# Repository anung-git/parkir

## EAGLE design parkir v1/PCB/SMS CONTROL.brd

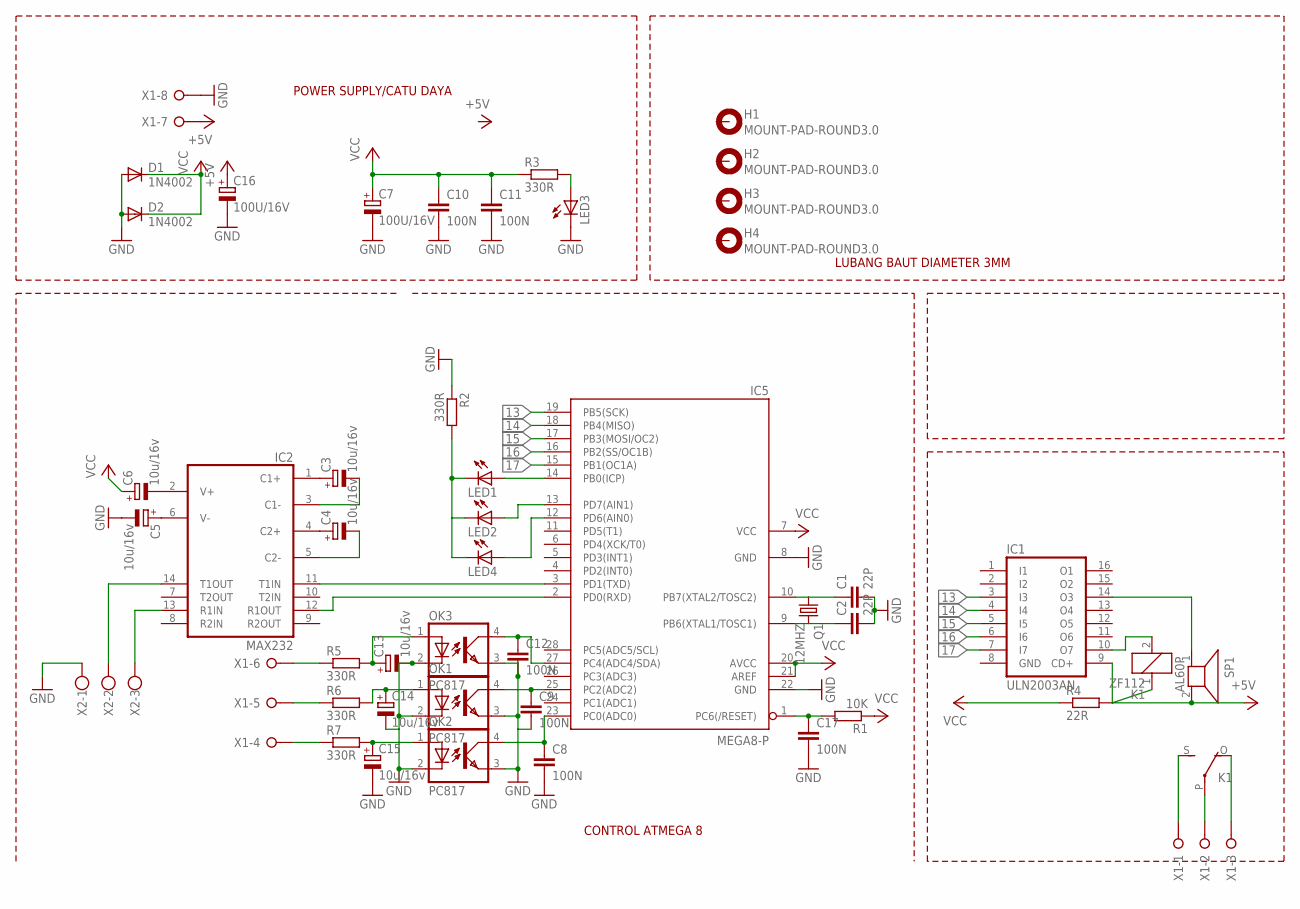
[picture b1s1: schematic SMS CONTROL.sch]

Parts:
C1, C2: 22P; C025-025X050
C3, C4, C5, C6, C13, C14, C15: 10u/16v; E2,5-6
C7, C16: 100U/16V; E2,5-6
C8, C9, C11, C12, C17: 100N; C025-025X050
C10: 100N; C075-032X103
D1, D2: 1N4002; DO35-10
H1, H2, H3, H4: MOUNT-PAD-ROUND3.0; 3,0-PAD
IC1: ULN2003AN; DIL16
IC2: MAX232; DIL16
IC5: MEGA8-P; DIL28-3
K1: ZF112
LED1, LED2, LED3, LED4: LED5MM
OK1, OK2, OK3: PC817; DIL04
Q1: 12MHZ; HC49U-V
R1: 10K; 0207/10
R2, R3, R5, R6, R7: 330R; 0207/10
R4: 22R; 0207/10
SP1: AL60P
X1: W237-08P; W237-8P
X2: W237-103

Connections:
13: IC1.3 (I3), IC5.19 (PB5(SCK))
14: IC1.4 (I4), IC5.18 (PB4(MISO))
15: IC1.5 (I5), IC5.17 (PB3(MOSI/OC2))
16: IC1.6 (I6), IC5.16 (PB2(SS/OC1B))
17: IC1.7 (I7), IC5.15 (PB1(OC1A))
+5V: C16.+, IC1.9 (CD+), K1.1, R4.2, SP1.2, X1.7
GND: C1.2, C2.2, C5.-, C7.-, C8.2, C9.2, C10.2, C11.2, C12.2, C13.-, C14.-, C15.-, C16.-, C17.2, D1.A, D2.A, IC1.8 (GND), IC2.15 (GND), IC5.8 (GND), IC5.22 (GND), LED3.K (C), OK1.2 (C), OK1.3 (EMIT), OK2.2 (C), OK2.3 (EMIT), OK3.2 (C), OK3.3 (EMIT), R2.1, X1.8, X2.1
unnamed: C17.1, IC5.1 (PC6(/RESET)), R1.2
unnamed: C13.+, OK3.1 (A), R5.2
unnamed: C14.+, OK1.1 (A), R6.2
unnamed: C9.1, IC5.25 (PC2(ADC2)), OK1.4 (COL)
unnamed: C12.1, IC5.27 (PC4(ADC4/SDA)), OK3.4 (COL)
unnamed: C15.+, OK2.1 (A), R7.2
unnamed: R5.1, X1.6
unnamed: IC5.14 (PB0(ICP)), LED1.A
unnamed: IC2.12 (R1OUT), IC5.2 (PD0(RXD))
unnamed: IC2.11 (T1IN), IC5.3 (PD1(TXD))
unnamed: C2.1, IC5.9 (PB6(XTAL1/TOSC1)), Q1.2
unnamed: C1.1, IC5.10 (PB7(XTAL2/TOSC2)), Q1.1
unnamed: LED3.A, R3.2
unnamed: R6.1, X1.5
unnamed: C3.+, IC2.1 (C1+)
unnamed: C3.-, IC2.3 (C1-)
unnamed: C8.1, IC5.23 (PC0(ADC0)), OK2.4 (COL)
unnamed: IC5.13 (PD7(AIN1)), LED2.A
unnamed: LED1.K (C), LED2.K (C), LED4.K (C), R2.2
unnamed: R7.1, X1.4
unnamed: C4.+, IC2.4 (C2+)
unnamed: C4.-, IC2.5 (C2-)
unnamed: C5.+, IC2.6 (V-)
unnamed: C6.-, IC2.2 (V+)
unnamed: IC2.13 (R1IN), X2.3
unnamed: IC2.14 (T1OUT), X2.2
unnamed: IC5.12 (PD6(AIN0)), LED4.A
unnamed: K1.S, X1.1
unnamed: K1.P, X1.2
unnamed: K1.O, X1.3
unnamed: IC1.10 (O7), K1.2
unnamed: IC1.14 (O3), SP1.1
VCC: C6.+, C7.+, C10.1, C11.1, D1.C, D2.C, IC2.16 (VCC), IC5.7 (VCC), IC5.20 (AVCC), IC5.21 (AREF), R1.1, R3.1, R4.1

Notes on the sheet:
POWER SUPPLY/CATU DAYA
CONTROL ATMEGA 8
LUBANG BAUT DIAMETER 3MM

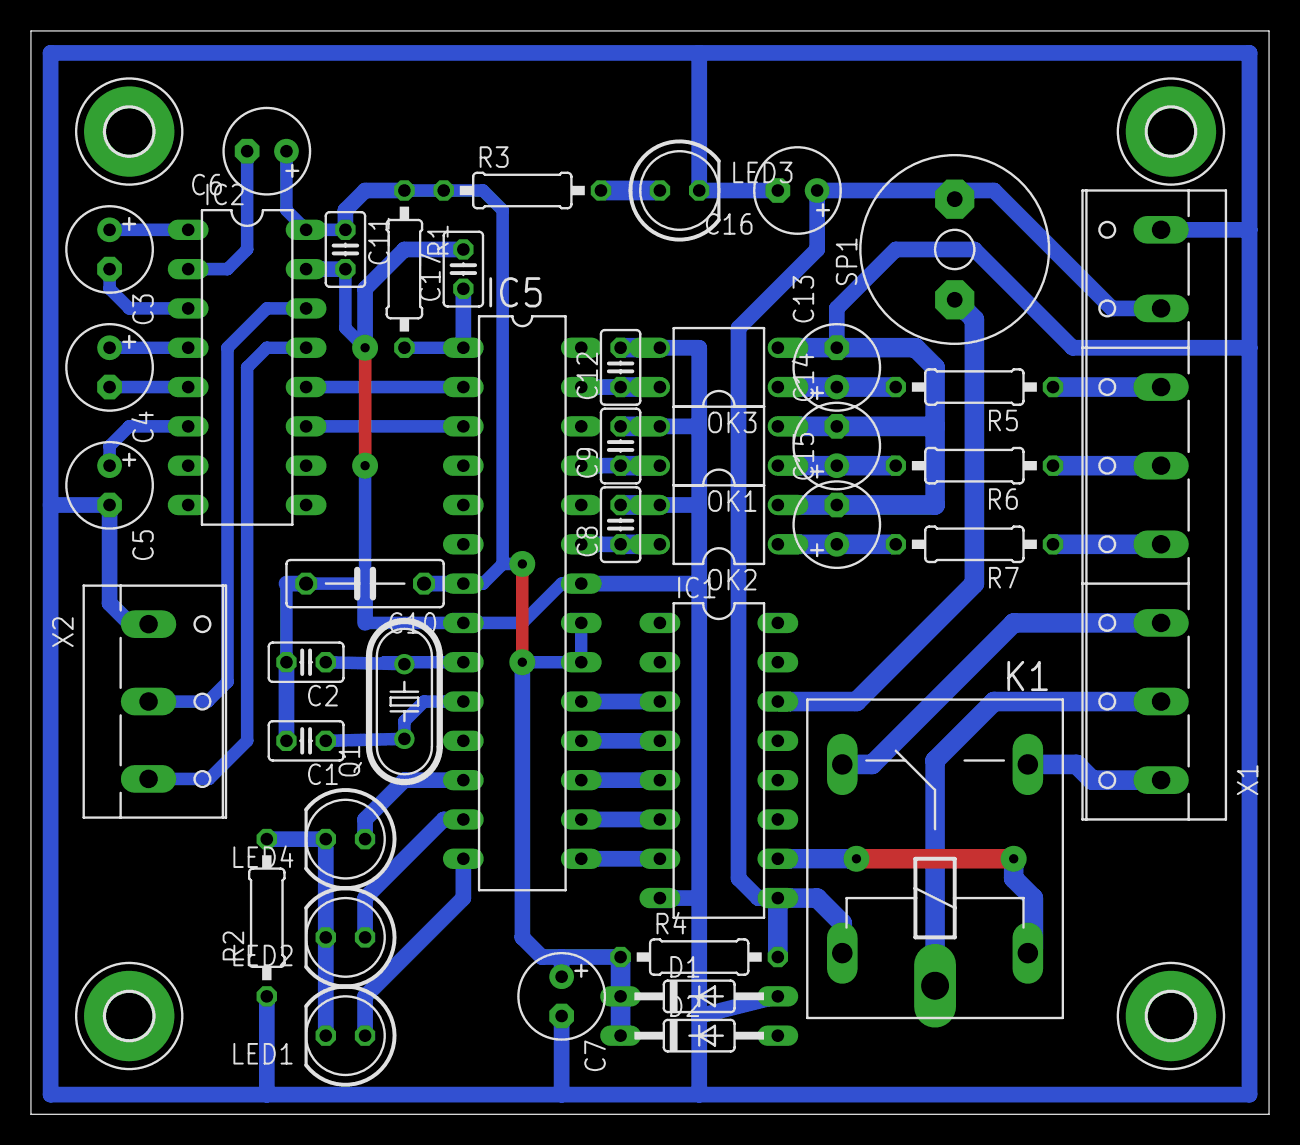
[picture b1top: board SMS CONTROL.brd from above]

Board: 2 copper layers, 80.0 x 70.0 mm, 45 parts (0 on the bottom side), 40 nets.

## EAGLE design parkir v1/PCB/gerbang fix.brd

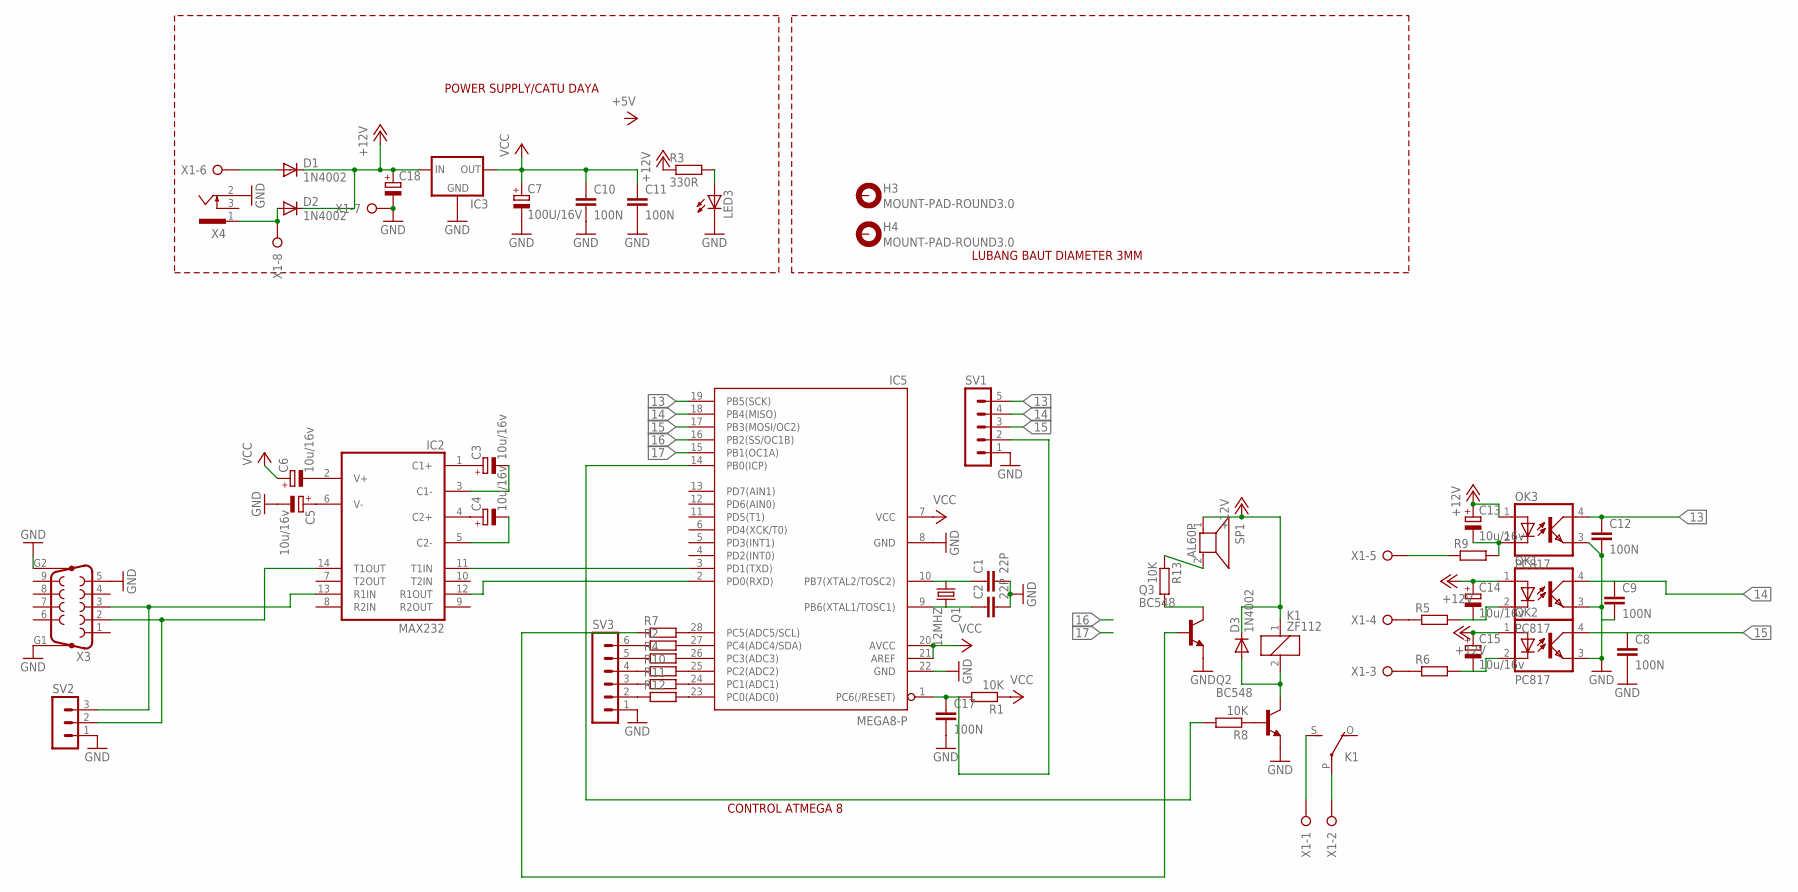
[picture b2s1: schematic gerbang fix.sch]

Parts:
C1, C2: 22P; C025-025X050
C3, C4, C5, C6, C13, C14, C15: 10u/16v; E2,5-6
C7: 100U/16V; E2,5-6
C8, C9, C10, C11, C12, C17: 100N; C025-025X050
C18: CPOL-EUE5-8.5; E5-8,5
D1, D2, D3: 1N4002; DO35-10
H3, H4: MOUNT-PAD-ROUND3.0; 3,0-PAD
IC2: MAX232; DIL16
IC3: 78XXS
IC5: MEGA8-P; DIL28-3
K1: ZF112
LED3: LED5MM
OK1, OK2, OK3: PC817; DIL04
Q1: 12MHZ; HC49U-V
Q2, Q3: BC548; TO92-EBC
R1, R8, R13: 10K; 0207/10
R2, R4, R5, R6, R7, R9, R10, R11, R12: R-EU_0204/2V; 0204V
R3: 330R; 0207/10
SP1: AL60P
SV1: MA05-1
SV2: MA03-1
SV3: MA06-1
X1: W237-08P; W237-8P
X3: F09HP
X4: 733980-62

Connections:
13: C12.1, IC5.19 (PB5(SCK)), OK3.4 (COL), SV1.5
14: C9.1, IC5.18 (PB4(MISO)), OK1.4 (COL), SV1.4
15: C8.1, IC5.17 (PB3(MOSI/OC2)), OK2.4 (COL), SV1.3
16: IC5.16 (PB2(SS/OC1B))
17: IC5.15 (PB1(OC1A))
+12V: C13.+, C14.+, C15.+, C18.+, D1.C, D2.C, D3.C, IC3.IN, K1.1, OK1.1 (A), OK2.1 (A), OK3.1 (A), R3.1, SP1.1
GND: C1.2, C2.2, C5.-, C7.-, C8.2, C9.2, C10.2, C11.2, C12.2, C17.2, C18.-, IC2.15 (GND), IC3.GND, IC5.8 (GND), IC5.22 (GND), LED3.K (C), OK1.3 (EMIT), OK2.3 (EMIT), OK3.3 (EMIT), Q2.E, Q3.E, SV1.1, SV2.1, SV3.1, X1.7, X3.5, X3.G1, X3.G2, X4.2
unnamed: C17.1, IC5.1 (PC6(/RESET)), R1.2, SV1.2
unnamed: Q3.C, R13.2
unnamed: Q3.B, R7.1
unnamed: IC5.14 (PB0(ICP)), R8.2
unnamed: R13.1, SP1.2
unnamed: R9.1, X1.5
unnamed: D1.A, X1.6
unnamed: IC2.12 (R1OUT), IC5.2 (PD0(RXD))
unnamed: IC2.11 (T1IN), IC5.3 (PD1(TXD))
unnamed: C2.1, IC5.9 (PB6(XTAL1/TOSC1)), Q1.2
unnamed: C1.1, IC5.10 (PB7(XTAL2/TOSC2)), Q1.1
unnamed: LED3.A, R3.2
unnamed: R5.1, X1.4
unnamed: C3.+, IC2.1 (C1+)
unnamed: C3.-, IC2.3 (C1-)
unnamed: D2.A, X1.8, X4.1
unnamed: IC5.27 (PC4(ADC4/SDA)), R2.2
unnamed: R6.1, X1.3
unnamed: C4.+, IC2.4 (C2+)
unnamed: C4.-, IC2.5 (C2-)
unnamed: C5.+, IC2.6 (V-)
unnamed: C6.-, IC2.2 (V+)
unnamed: IC2.13 (R1IN), SV2.3, X3.3
unnamed: IC2.14 (T1OUT), SV2.2, X3.2
unnamed: IC5.28 (PC5(ADC5/SCL)), R7.2
unnamed: K1.S, X1.1
unnamed: K1.P, X1.2
unnamed: C13.-, OK3.2 (C), R9.2
unnamed: C14.-, OK1.2 (C), R5.2
unnamed: C15.-, OK2.2 (C), R6.2
unnamed: D3.A, K1.2, Q2.C
unnamed: IC5.26 (PC3(ADC3)), R4.2
unnamed: Q2.B, R8.1
unnamed: IC5.25 (PC2(ADC2)), R10.2
unnamed: IC5.24 (PC1(ADC1)), R11.2
unnamed: IC5.23 (PC0(ADC0)), R12.2
unnamed: R2.1, SV3.6
unnamed: R4.1, SV3.5
unnamed: R10.1, SV3.4
unnamed: R11.1, SV3.3
unnamed: R12.1, SV3.2
VCC: C6.+, C7.+, C10.1, C11.1, IC2.16 (VCC), IC3.OUT, IC5.7 (VCC), IC5.20 (AVCC), IC5.21 (AREF), R1.1

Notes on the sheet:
POWER SUPPLY/CATU DAYA
CONTROL ATMEGA 8
LUBANG BAUT DIAMETER 3MM

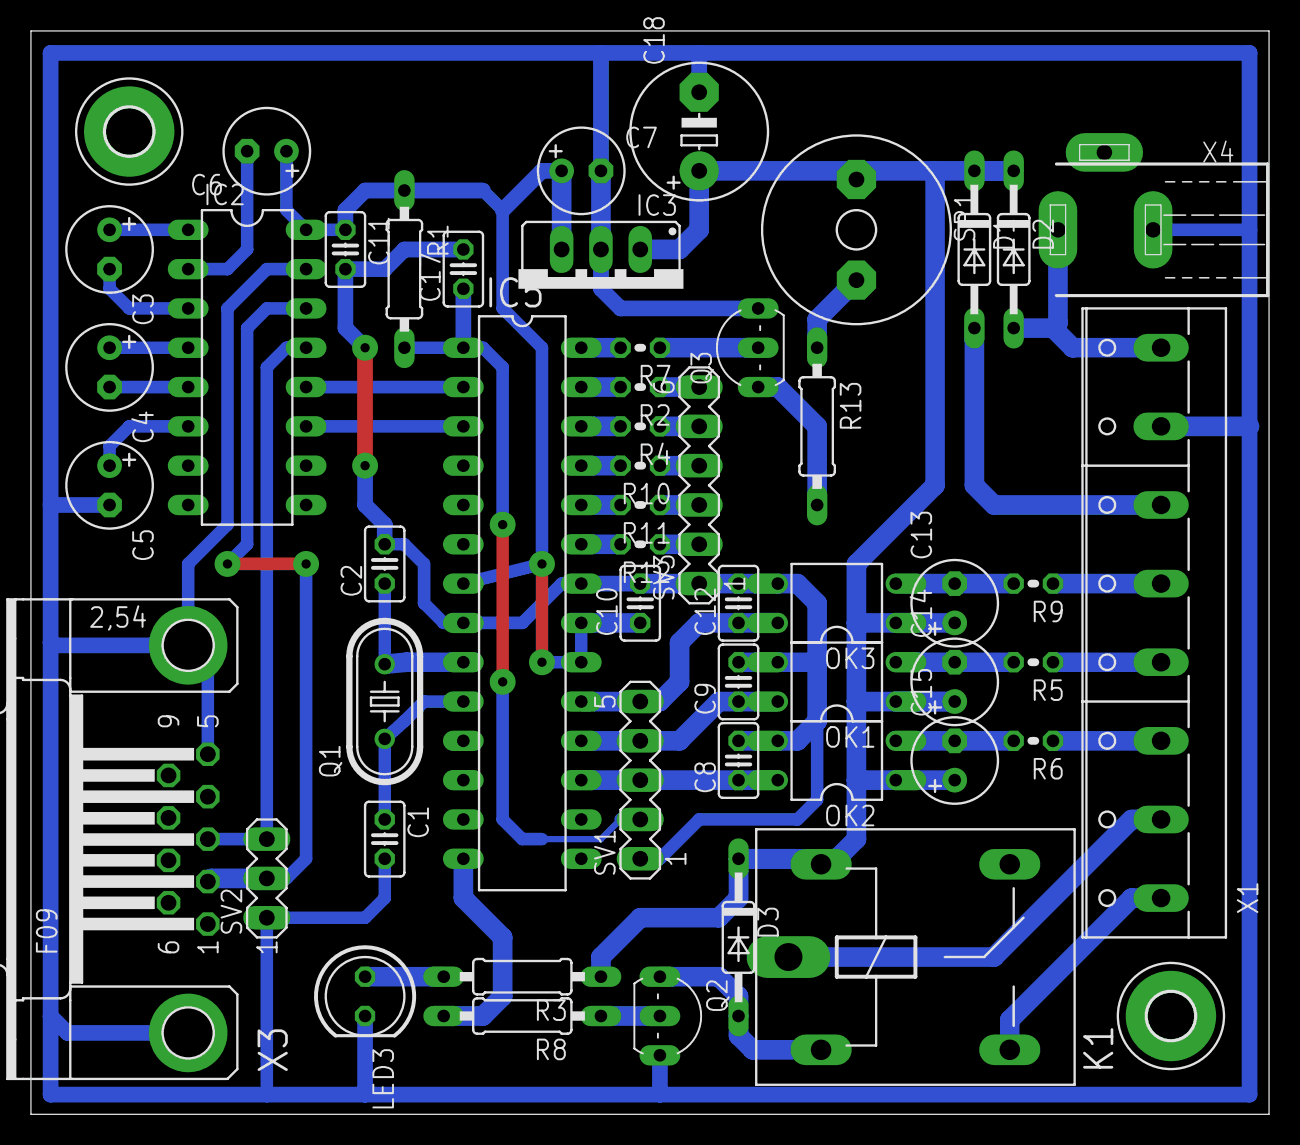
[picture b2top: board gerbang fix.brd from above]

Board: 2 copper layers, 80.0 x 70.0 mm, 53 parts (0 on the bottom side), 47 nets.

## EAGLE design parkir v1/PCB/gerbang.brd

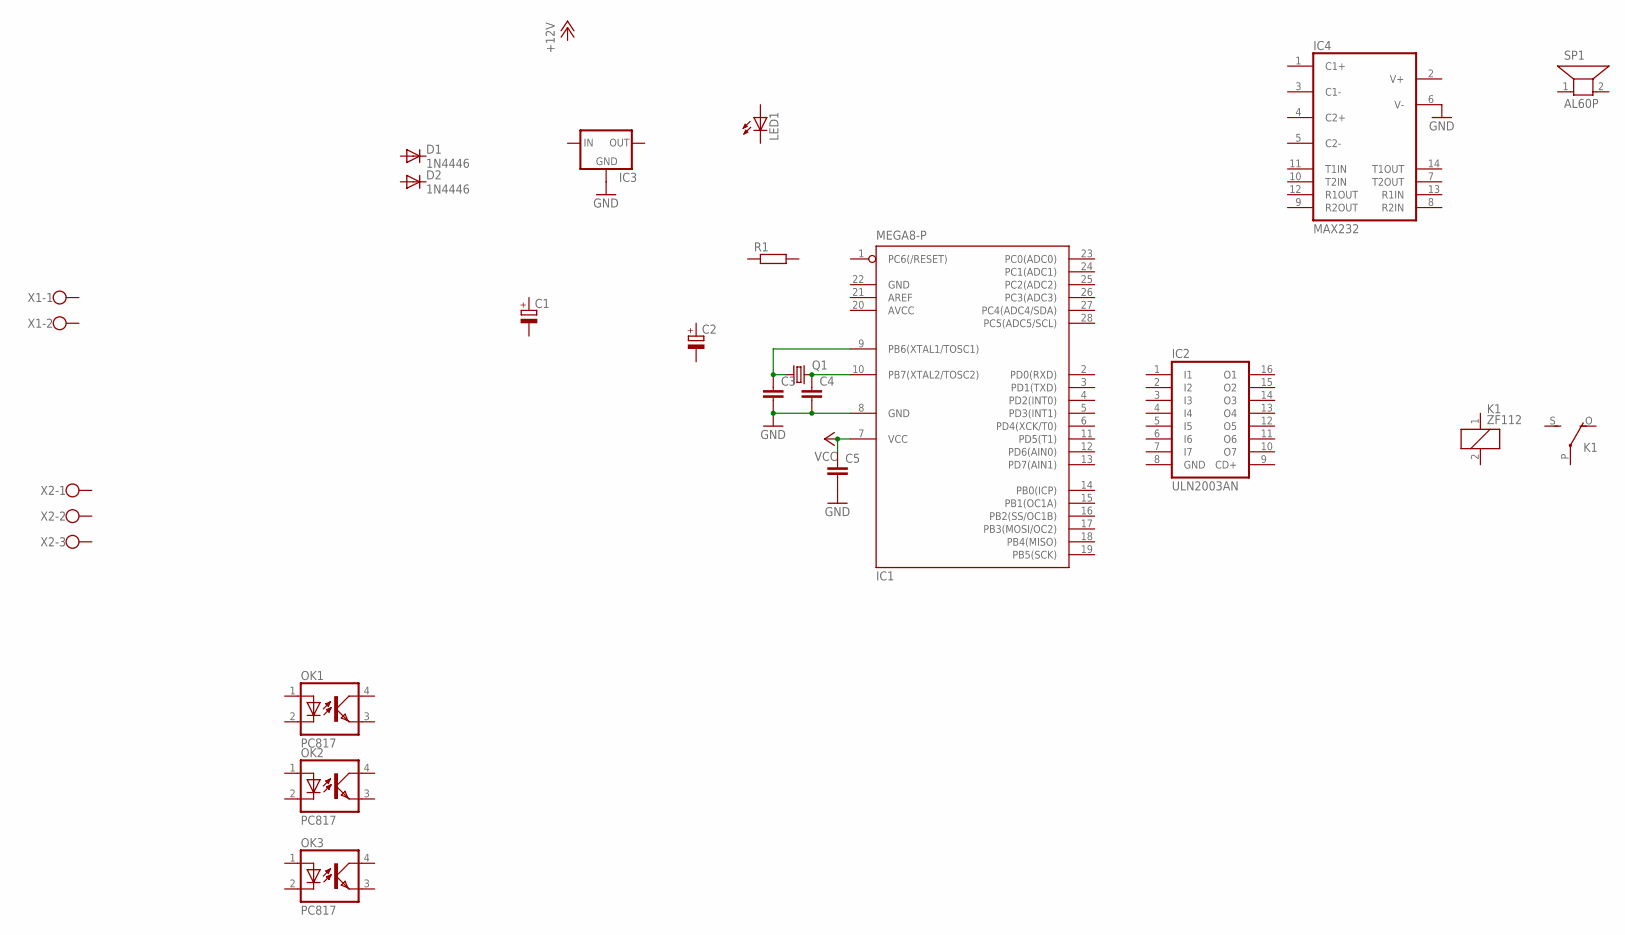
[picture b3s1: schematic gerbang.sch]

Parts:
C1: CPOL-EUE5-8.5; E5-8,5
C2: CPOL-EUE2.5-5; E2,5-5
C3, C4: C-EU025-025X050; C025-025X050
C5: C-EU050-025X075; C050-025X075
D1, D2: 1N4446; DO35-10
IC1: MEGA8-P; DIL28-3
IC2: ULN2003AN; DIL16
IC3: 78XXS
IC4: MAX232; DIL16
K1: ZF112
LED1: LED5MM
OK1, OK2, OK3: PC817; DIL04
Q1: CRYSTALHC49S; HC49/S
R1: R-EU_0207/10; 0207/10
SP1: AL60P
X1: W237-102
X2: W237-103

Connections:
AVCC: IC1.20 (AVCC)
GND: C3.2, C4.2, C5.2, IC1.8 (GND), IC1.22 (GND), IC2.8 (GND), IC3.GND, IC4.6 (V-), IC4.15 (GND)
unnamed: C3.1, IC1.9 (PB6(XTAL1/TOSC1)), Q1.1
unnamed: C4.1, IC1.10 (PB7(XTAL2/TOSC2)), Q1.2
VCC: C5.1, IC1.7 (VCC), IC4.16 (VCC)

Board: 2 copper layers, 21 parts (0 on the bottom side), 4 nets, no tracks yet.

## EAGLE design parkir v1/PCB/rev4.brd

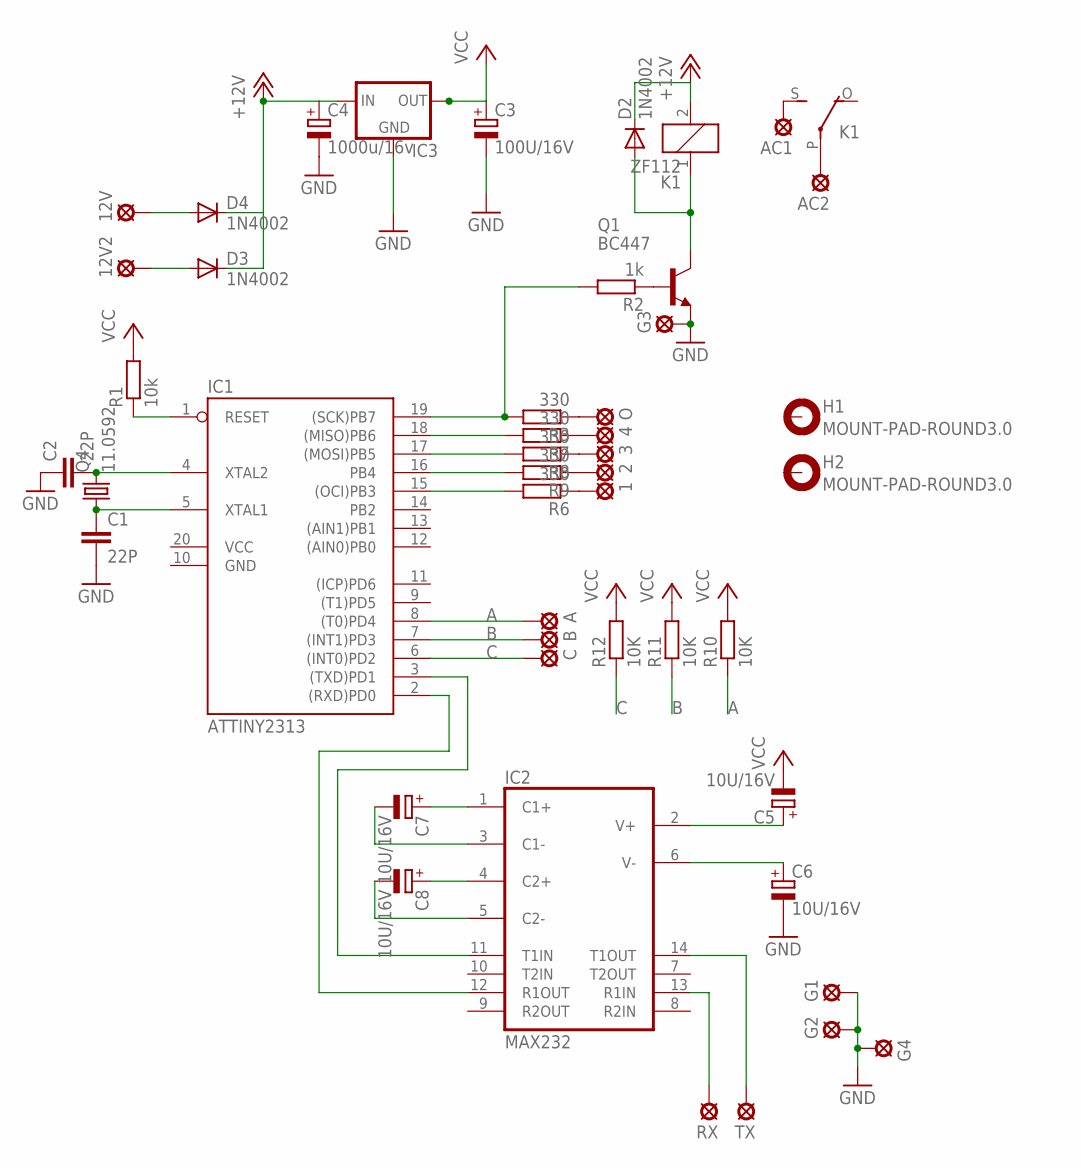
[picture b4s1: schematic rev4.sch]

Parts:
1, 2, 3, 4, 12V, 12V2: MCS10B
A: MCS10B
AC1, AC2: MCS10B
B: MCS10B
C: MCS10B
C1, C2: 22P; C025-025X050
C3: 100U/16V; E2,5-5
C4: 1000u/16v; E5-6
C5, C6, C7, C8: 10U/16V; E2,5-5
D2, D3, D4: 1N4002; DO35-7
G1, G2, G3, G4: MCS10B
H1, H2: MOUNT-PAD-ROUND3.0; 3,0-PAD
IC1: ATTINY2313; DIL20
IC2: MAX232; DIL16
IC3: 78XXS
K1: ZF112
O: MCS10B
Q1: BC447; TO92-EBC
Q4: 11.0592; HC49/S
R1: 10k; 0207/7
R2: 1k; 0207/7
R3, R6, R7, R8, R9: 330; 0207/7
R10, R11, R12: 10K; 0207/7
RX: MCS10B
TX: MCS10B

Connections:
+12V: C4.+, D2.C, D3.C, D4.C, IC3.IN, K1.2
A: A.MP, IC1.8 ((T0)PD4), R10.1
B: B.MP, IC1.7 ((INT1)PD3), R11.1
C: C.MP, IC1.6 ((INT0)PD2), R12.1
GND: C1.2, C2.1, C3.-, C4.-, C6.-, G1.MP, G2.MP, G3.MP, G4.MP, IC1.10 (GND), IC2.15 (GND), IC3.GND, Q1.E
MISO: IC1.18 ((MISO)PB6), R7.2
MOSI: IC1.17 ((MOSI)PB5), R8.2
unnamed: C5.+, IC2.2 (V+)
unnamed: C2.2, IC1.4 (XTAL2), Q4.2
unnamed: C1.1, IC1.5 (XTAL1), Q4.1
unnamed: 12V2.MP, D3.A
unnamed: Q1.B, R2.1
unnamed: C6.+, IC2.6 (V-)
unnamed: IC2.14 (T1OUT), TX.MP
unnamed: D2.A, K1.1, Q1.C
unnamed: IC1.15 ((OCI)PB3), R6.2
unnamed: IC2.13 (R1IN), RX.MP
unnamed: IC1.3 ((TXD)PD1), IC2.11 (T1IN)
unnamed: IC1.2 ((RXD)PD0), IC2.12 (R1OUT)
unnamed: AC2.MP, K1.P
unnamed: AC1.MP, K1.S
unnamed: 12V.MP, D4.A
unnamed: IC1.16 (PB4), R9.2
unnamed: 1.MP, R6.1
unnamed: 2.MP, R9.1
unnamed: 3.MP, R8.1
unnamed: 4.MP, R7.1
unnamed: C7.+, IC2.1 (C1+)
unnamed: O.MP, R3.1
unnamed: C8.+, IC2.4 (C2+)
unnamed: C7.-, IC2.3 (C1-)
unnamed: C8.-, IC2.5 (C2-)
RESET: IC1.1 (RESET), R1.1
SCK: IC1.19 ((SCK)PB7), R2.2, R3.2
VCC: C3.+, C5.-, IC1.20 (VCC), IC2.16 (VCC), IC3.OUT, R1.2, R10.2, R11.2, R12.2

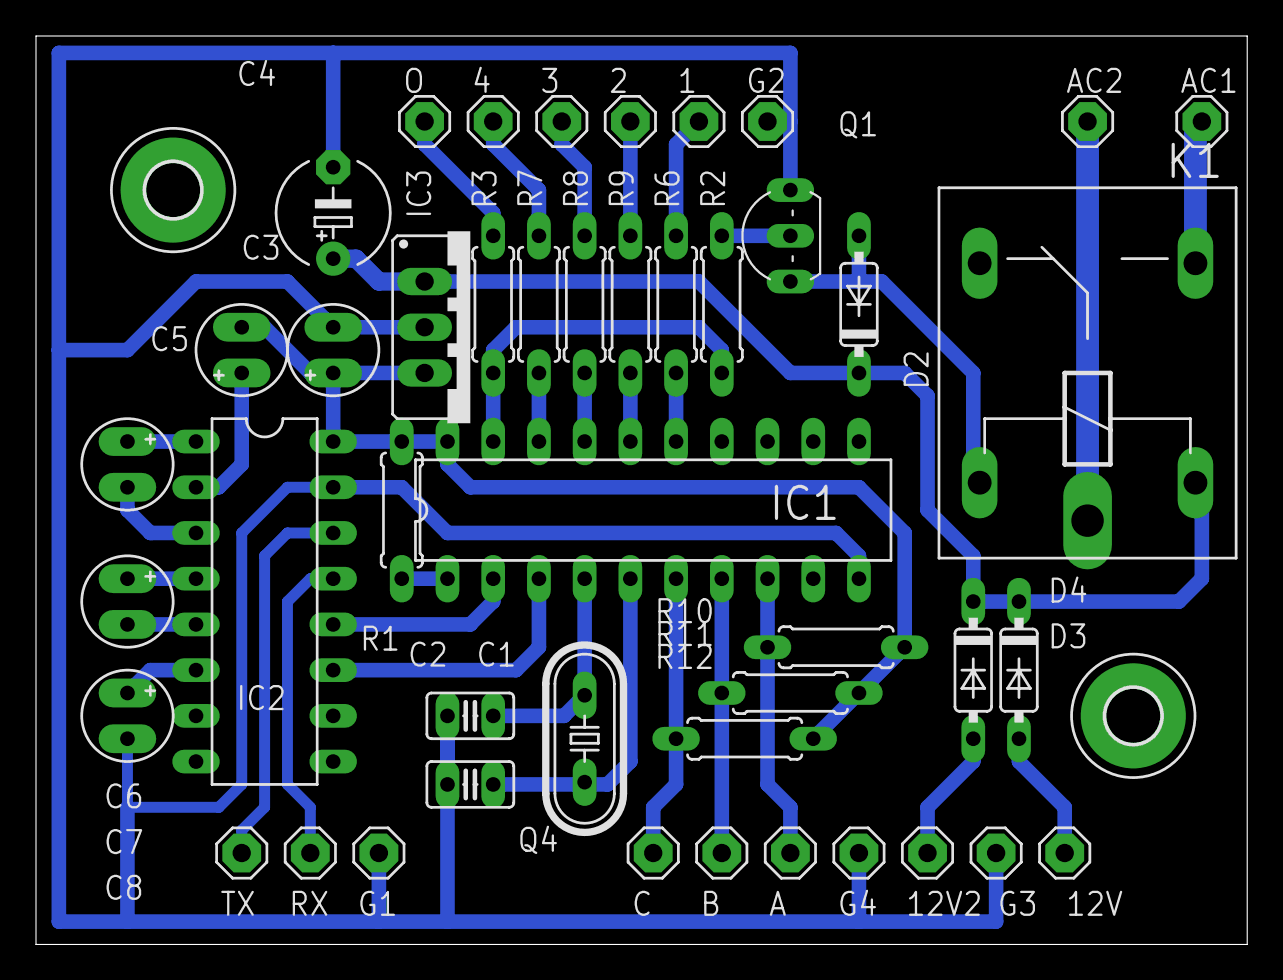
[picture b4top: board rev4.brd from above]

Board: 2 copper layers, 67.3 x 50.5 mm, 47 parts (0 on the bottom side), 35 nets.
